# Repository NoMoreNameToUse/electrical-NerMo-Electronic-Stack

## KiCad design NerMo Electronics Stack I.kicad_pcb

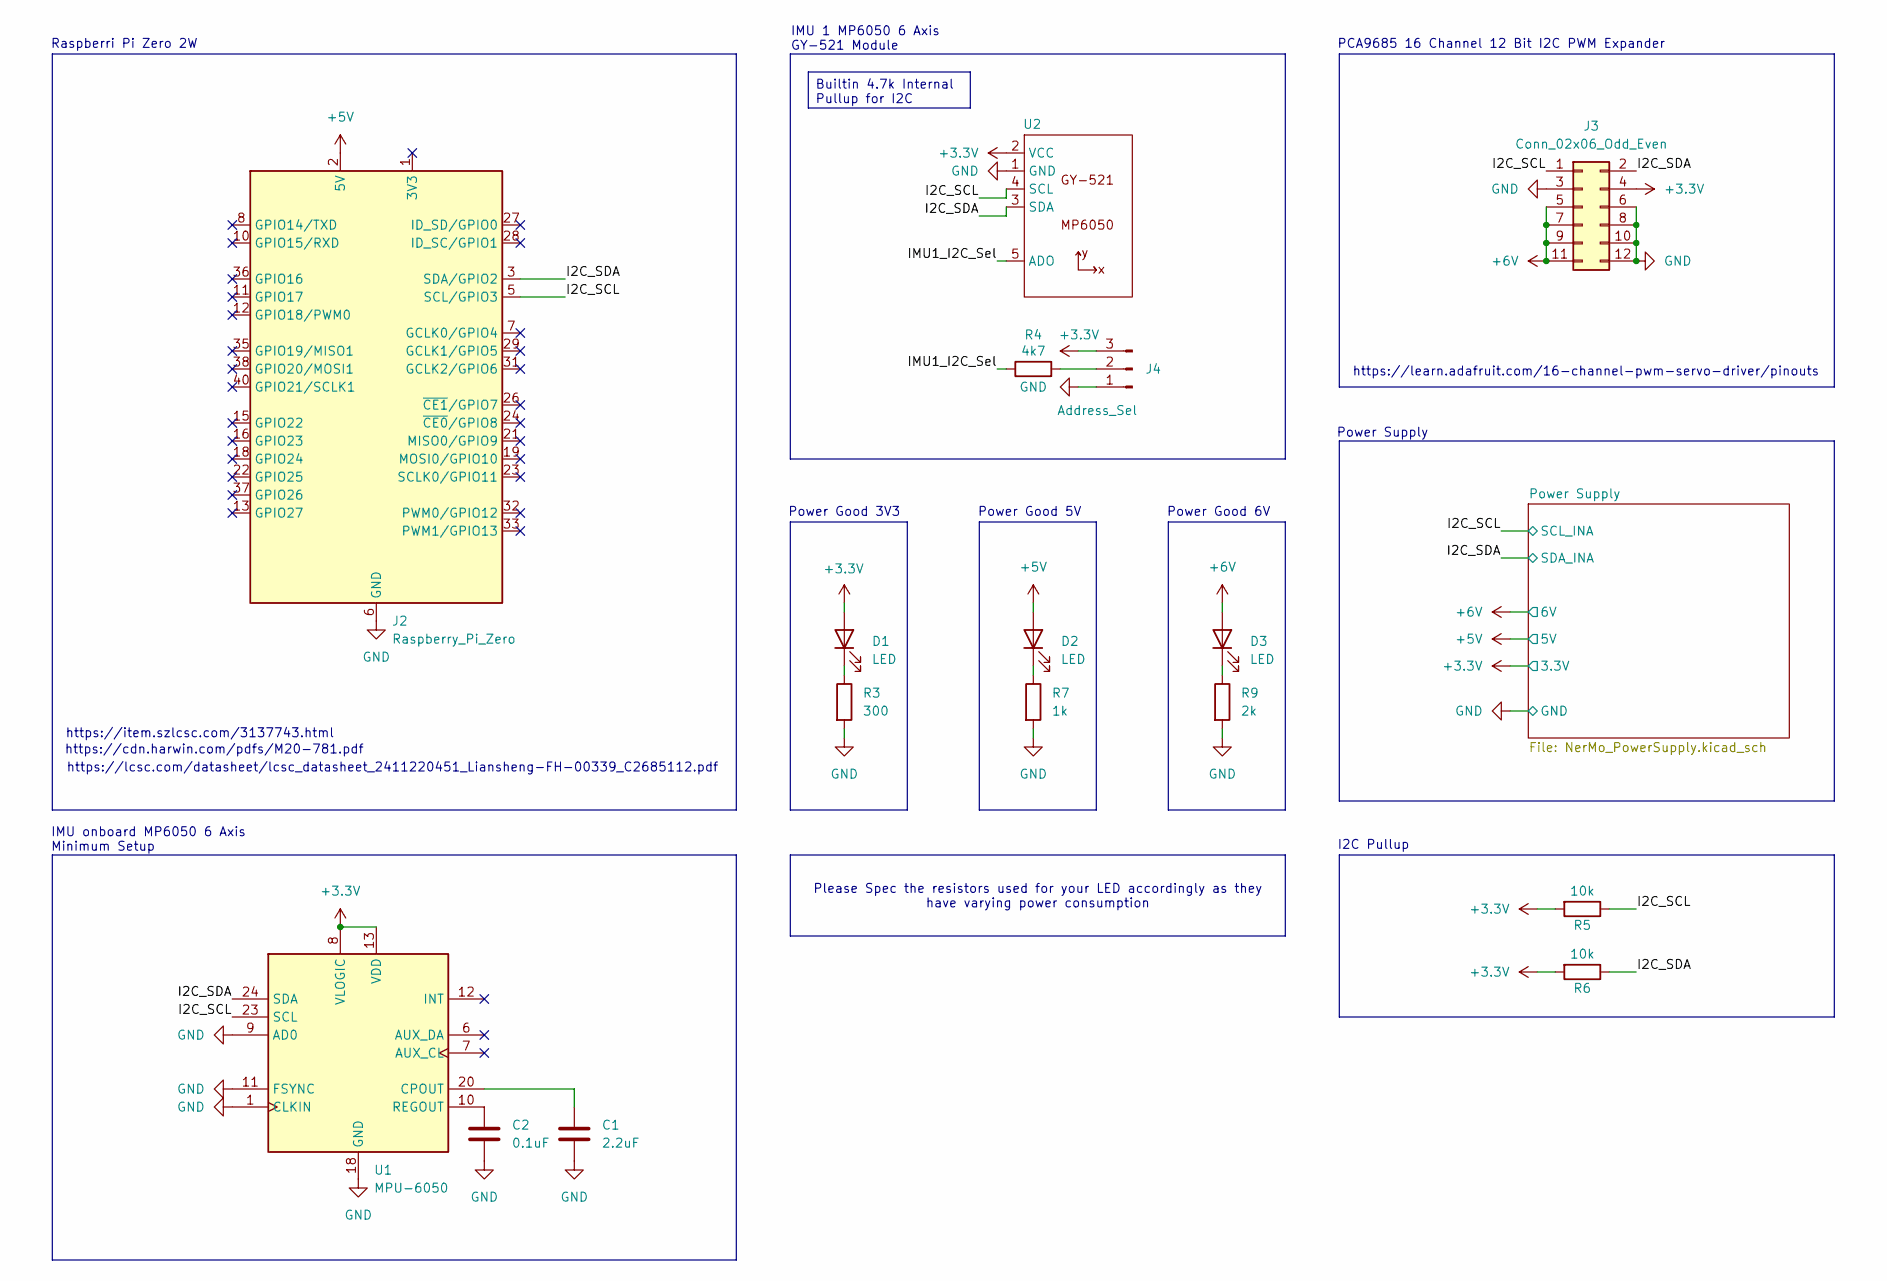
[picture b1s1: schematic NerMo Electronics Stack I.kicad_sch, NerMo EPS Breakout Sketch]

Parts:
C1: 2.2uF; C_0805_2012Metric
C2: 0.1uF; C_0805_2012Metric
D1, D2, D3: LED; LED_0805_2012Metric_Pad1.15x1.40mm_HandSolder
J2: Raspberry_Pi_Zero; Raspberry_Pi_Zero_2_W_HDR-TH
J3: Conn_02x06_Odd_Even; PinSocket_2x06_P1.27mm_Vertical
J4: Address_Sel; SolderJumper-3_P1.3mm_Open_Pad1.0x1.5mm
R3: 300; R_0805_2012Metric
R4: 4k7; R_0805_2012Metric
R5, R6: 10k; R_0805_2012Metric
R7: 1k; R_0805_2012Metric
R9: 2k; R_0805_2012Metric
U1: MPU-6050; InvenSense_QFN-24_4x4mm_P0.5mm
U2: PinHeader_1x05_P2.54mm_Vertical

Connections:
+3.3V: D1.2 (A), J3.4, J4.3, R5.2, R6.2, U1.8 (VLOGIC), U1.13 (VDD), U2.2 (VCC); also elsewhere on the board
+5V: D2.2 (A), J2.2 (5V), J2.4 (5V); also elsewhere on the board
+6V: D3.2 (A), J3.5, J3.7, J3.9, J3.11; also elsewhere on the board
/I2C_SCL: J2.5 (SCL/GPIO3), J3.1, R5.1, U1.23 (SCL), U2.4 (SCL); also elsewhere on the board
/I2C_SDA: J2.3 (SDA/GPIO2), J3.2, R6.1, U1.24 (SDA), U2.3 (SDA); also elsewhere on the board
/IMU1_I2C_Sel: R4.1, U2.5 (ADO)
GND: C1.2, C2.2, J2.6 (GND), J2.9 (GND), J2.14 (GND), J2.20 (GND), J2.25 (GND), J2.30 (GND), J2.34 (GND), J2.39 (GND), J3.3, J3.6, J3.8, J3.10, J3.12, J4.1, R3.2, R7.2, R9.2, U1.1 (CLKIN), U1.9 (AD0), U1.11 (FSYNC), U1.18 (GND), U2.1 (GND); also elsewhere on the board
unnamed: D1.1 (K), R3.1
unnamed: D2.1 (K), R7.1
unnamed: D3.1 (K), R9.1
unnamed: J4.2, R4.2
unnamed: C1.1, U1.20 (CPOUT)
unnamed: C2.1, U1.10 (REGOUT)

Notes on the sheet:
https://cdn.harwin.com/pdfs/M20-781.pdf
https://learn.adafruit.com/16-channel-pwm-servo-driver/pinouts
https://item.szlcsc.com/3137743.html
https://lcsc.com/datasheet/lcsc_datasheet_2411220451_Liansheng-FH-00339_C2685112.pdf
PCA9685 16 Channel 12 Bit I2C PWM Expander
Power Good 6V
IMU onboard MP6050 6 Axis Minimum Setup
Power Good 3V3
Raspberri Pi Zero 2W
I2C Pullup
IMU 1 MP6050 6 Axis GY-521 Module
Power Good 5V
Power Supply
Please Spec the resistors used for your LED accordingly as they have varying power consumption
Builtin 4.7k Internal Pullup for I2C

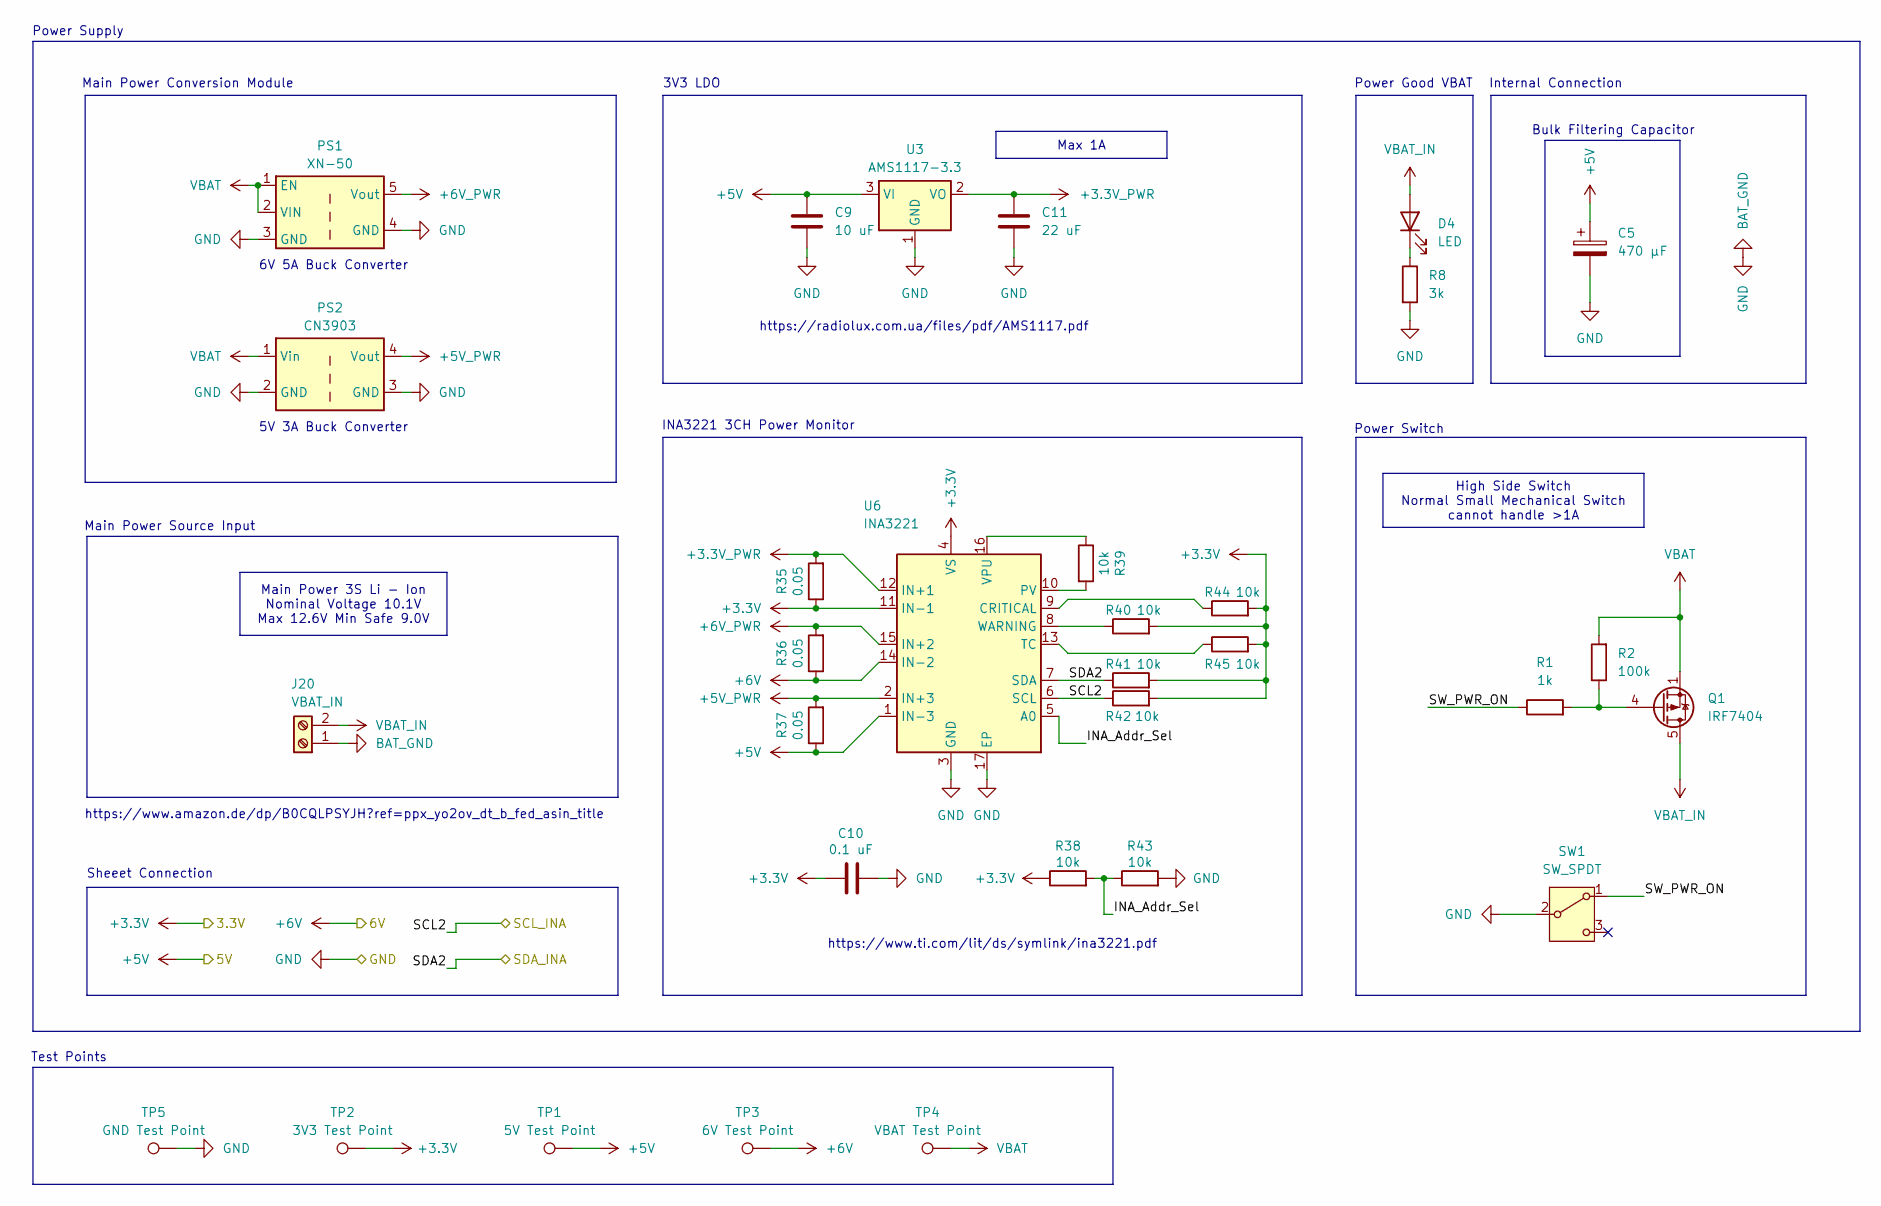
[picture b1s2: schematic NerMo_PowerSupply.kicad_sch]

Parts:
C5: 470 µF; CP_Elec_5x3
C9: 10 uF; C_0805_2012Metric
C10: 0.1 uF; C_0805_2012Metric
C11: 22 uF; C_0805_2012Metric
D4: LED; LED_0805_2012Metric_Pad1.15x1.40mm_HandSolder
J20: VBAT_IN; AMASS_XT30UPB-M_1x02_P5.0mm_Vertical
PS1: XN-50; XN-50 5A DCDC
PS2: CN3903; CN3903 3A DCDC
Q1: IRF7404; SOIC-8_3.9x4.9mm_P1.27mm
R1: 1k; R_0805_2012Metric
R2: 100k; R_0805_2012Metric
R8: 3k; R_0805_2012Metric
R35, R36, R37: 0.05; R_1206_3216Metric
R38, R39, R40, R41, R42, R43, R44, R45: 10k; R_0805_2012Metric
SW1: SW_SPDT; SW_SPDT_PCM12
TP1: 5V Test Point; TestPoint_Pad_2.0x2.0mm
TP2: 3V3 Test Point; TestPoint_Pad_2.0x2.0mm
TP3: 6V Test Point; TestPoint_Pad_2.0x2.0mm
TP4: VBAT Test Point; TestPoint_Pad_2.0x2.0mm
TP5: GND Test Point; TestPoint_Pad_2.0x2.0mm
U3: AMS1117-3.3; SOT-223-3_TabPin2
U6: INA3221; Texas_RGV0016A_VQFN-16-1EP_4x4mm_P0.65mm_EP2.1x2.1mm

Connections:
+3.3V: C10.1, R35.1, R38.1, R40.2, R41.2, R42.2, R44.2, R45.2, TP2.1, U6.4 (VS), U6.11 (IN-1); also elsewhere on the board
+3.3V_PWR: C11.1, R35.2, U3.2 (VO), U6.12 (IN+1)
+5V: C5.1, C9.1, R37.1, TP1.1, U3.3 (VI), U6.1 (IN-3); also elsewhere on the board
+5V_PWR: PS2.4 (Vout), R37.2, U6.2 (IN+3)
+6V: R36.1, TP3.1, U6.14 (IN-2); also elsewhere on the board
+6V_PWR: PS1.5 (Vout), R36.2, U6.15 (IN+2)
/I2C_SCL: R42.1, U6.6 (SCL); also elsewhere on the board
/I2C_SDA: R41.1, U6.7 (SDA); also elsewhere on the board
/Power Supply/INA_Addr_Sel: R38.2, R43.1, U6.5 (A0)
/Power Supply/SW_PWR_ON: R1.1, SW1.1 (A)
GND: C5.2, C9.2, C10.2, C11.2, J20.1, PS1.3 (GND), PS1.4 (GND), PS2.2 (GND), PS2.3 (GND), R8.2, R43.2, SW1.2 (B), TP5.1, U3.1 (GND), U6.3 (GND), U6.17 (EP); also elsewhere on the board
unnamed: D4.1 (K), R8.1
unnamed: Q1.4 (G), R1.2, R2.1
unnamed: R44.1, U6.9 (CRITICAL)
unnamed: R39.2, U6.10 (PV)
unnamed: R45.1, U6.13 (TC)
unnamed: R39.1, U6.16 (VPU)
unnamed: R40.1, U6.8 (WARNING)
VBAT: PS1.1 (EN), PS1.2 (VIN), PS2.1 (Vin), Q1.1 (S), Q1.2 (S), Q1.3 (S), R2.2, TP4.1
VBAT_IN: D4.2 (A), J20.2, Q1.5 (D), Q1.6 (D), Q1.7 (D), Q1.8 (D)

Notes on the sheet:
3V3 LDO
Main Power Source Input
INA3221 3CH Power Monitor
https://www.ti.com/lit/ds/symlink/ina3221.pdf
Test Points
5V 3A Buck Converter
Bulk Filtering Capacitor
Internal Connection
6V 5A Buck Converter
Power Switch
https://radiolux.com.ua/files/pdf/AMS1117.pdf
Power Good VBAT
Power Supply
Sheeet Connection
https://www.amazon.de/dp/B0CQLPSYJH?ref=ppx_yo2ov_dt_b_fed_asin_title
Main Power Conversion Module
Main Power 3S Li - Ion Nominal Voltage 10.1V Max 12.6V Min Safe 9.0V
Max 1A
High Side Switch Normal Small Mechanical Switch cannot handle >1A

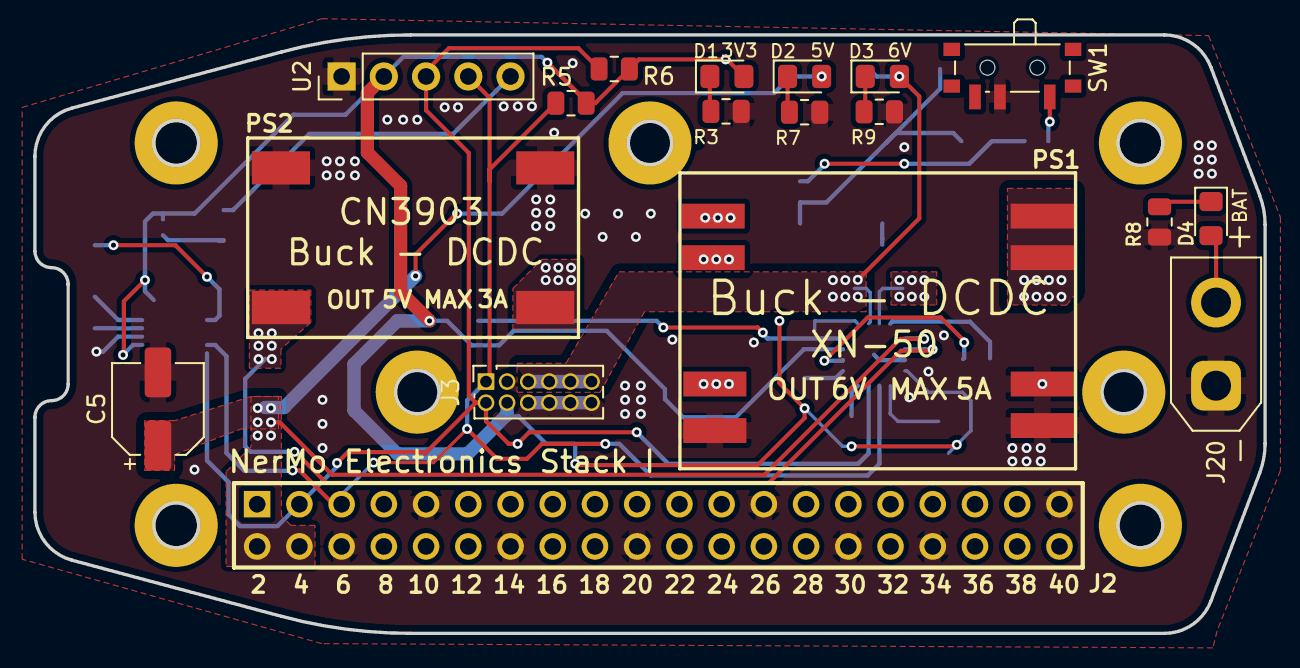
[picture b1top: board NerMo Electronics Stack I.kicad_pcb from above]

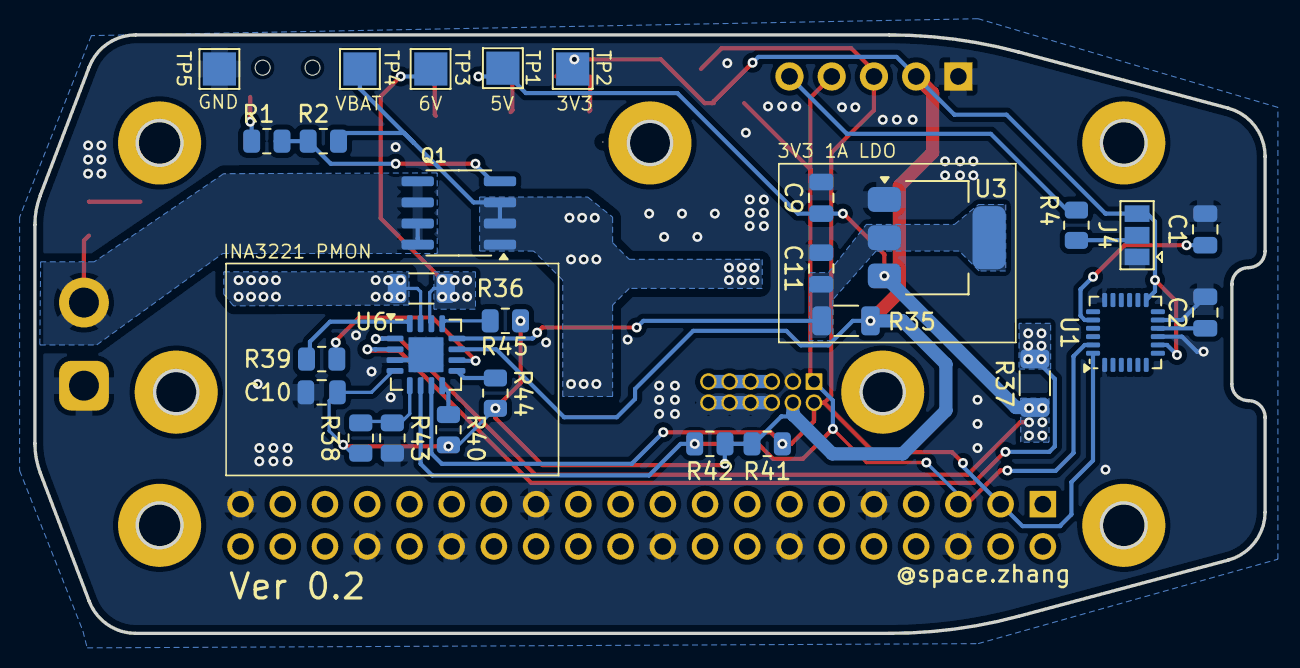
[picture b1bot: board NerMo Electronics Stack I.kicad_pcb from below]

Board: 2 copper layers, 74.0 x 36.0 mm, 54 parts (29 on the bottom side), 27 nets.

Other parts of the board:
*REF: (no value)
*REF#2, *REF#3, *REF#4, *REF#5, *REF#6, *REF#7: (no value)

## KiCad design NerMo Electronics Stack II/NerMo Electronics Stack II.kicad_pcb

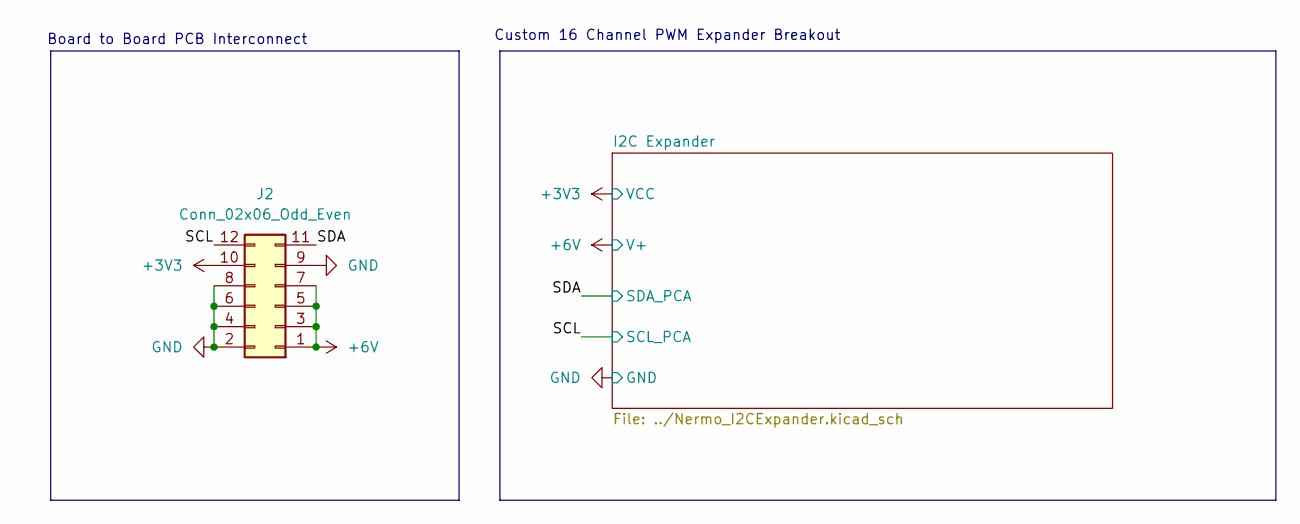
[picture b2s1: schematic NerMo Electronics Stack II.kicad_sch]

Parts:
J2: Conn_02x06_Odd_Even; PinHeader_2x06_P1.27mm_Vertical

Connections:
+3V3: J2.10; also elsewhere on the board
+6V: J2.1, J2.3, J2.5, J2.7; also elsewhere on the board
/SCL: J2.12; also elsewhere on the board
/SDA: J2.11; also elsewhere on the board
GND: J2.2, J2.4, J2.6, J2.8, J2.9; also elsewhere on the board

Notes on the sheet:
Board to Board PCB Interconnect
Custom 16 Channel PWM Expander Breakout

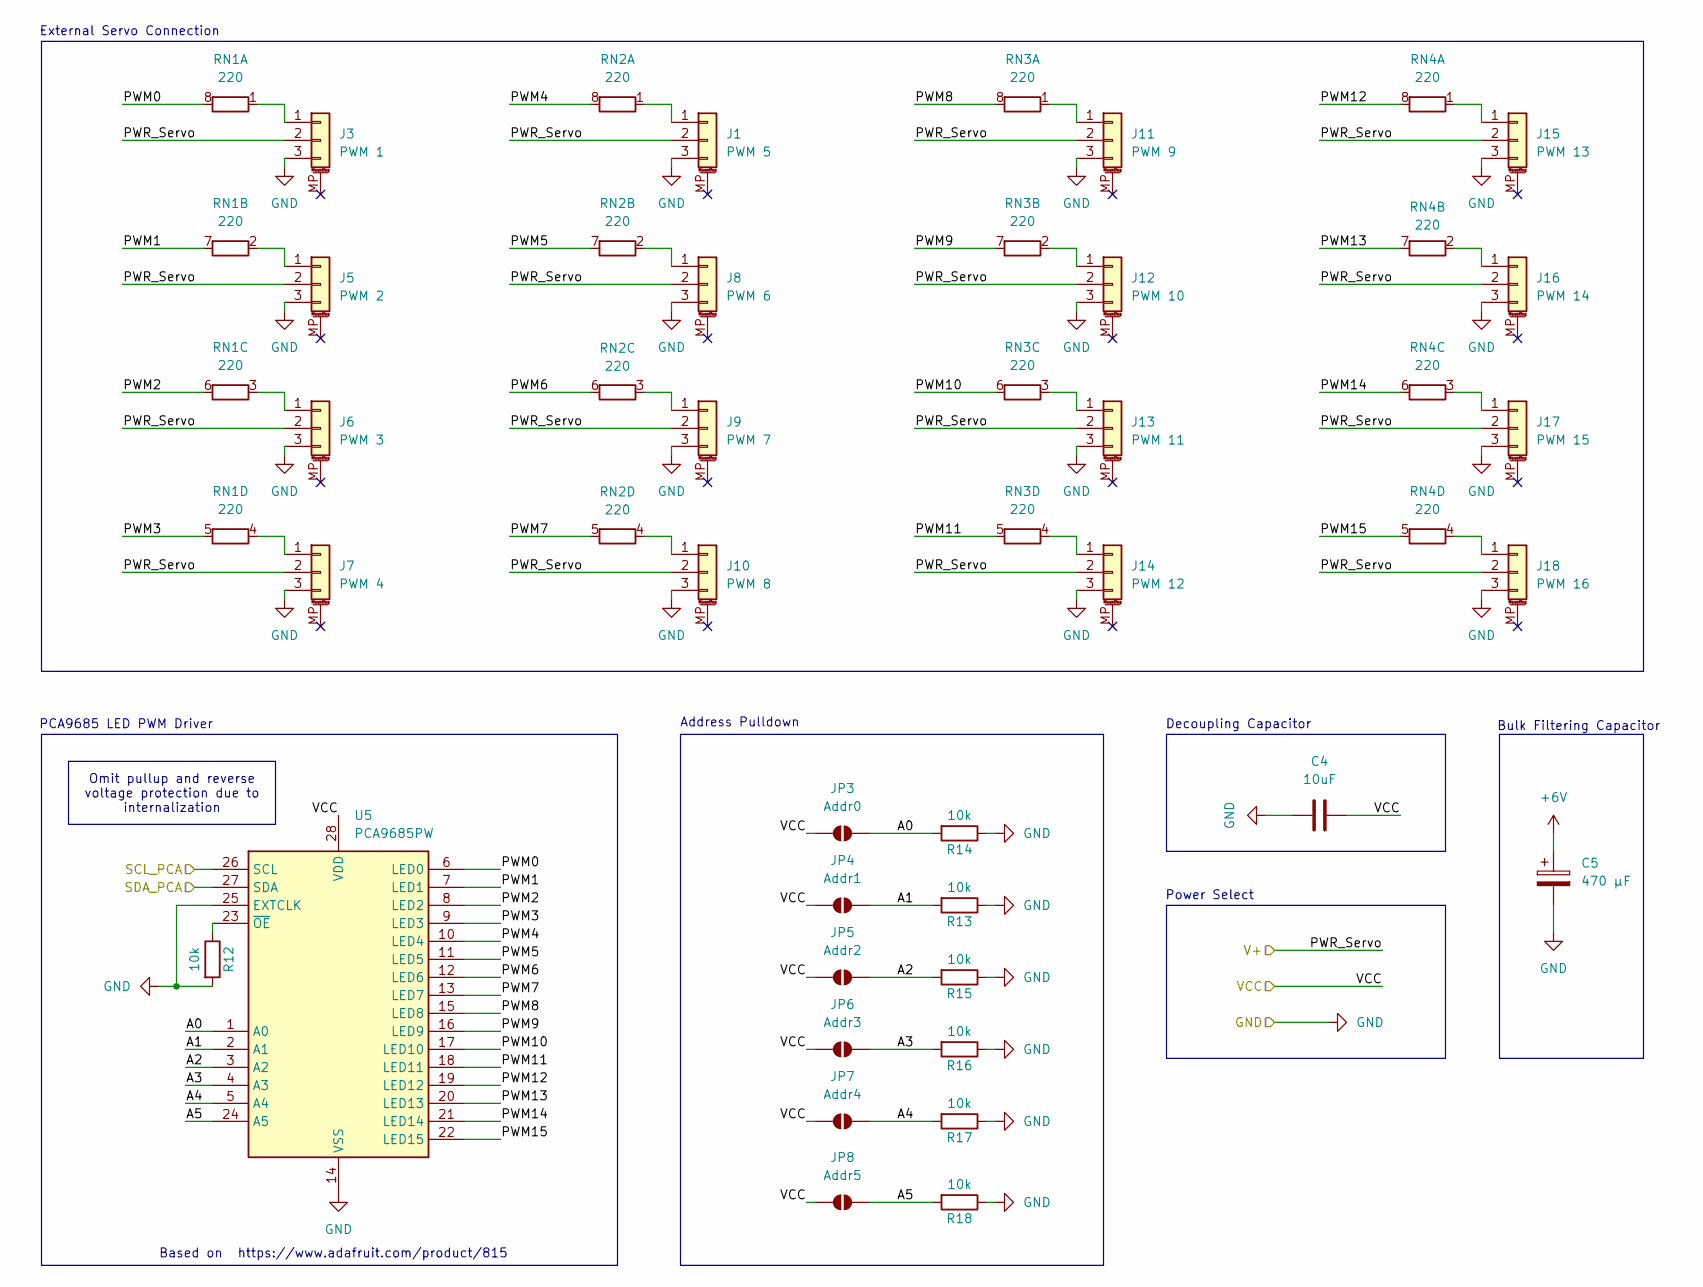
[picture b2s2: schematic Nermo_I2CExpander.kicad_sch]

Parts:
C4: 10uF; C_0603_1608Metric
C5: 470 µF; CP_EIA-7360-38_Kemet-E_HandSolder
J1: PWM 5; JST_SH_SM03B-SRSS-TB_1x03-1MP_P1.00mm_Horizontal
J3: PWM 1; JST_SH_SM03B-SRSS-TB_1x03-1MP_P1.00mm_Horizontal
J5: PWM 2; JST_SH_SM03B-SRSS-TB_1x03-1MP_P1.00mm_Horizontal
J6: PWM 3; JST_SH_SM03B-SRSS-TB_1x03-1MP_P1.00mm_Horizontal
J7: PWM 4; JST_SH_SM03B-SRSS-TB_1x03-1MP_P1.00mm_Horizontal
J8: PWM 6; JST_SH_SM03B-SRSS-TB_1x03-1MP_P1.00mm_Horizontal
J9: PWM 7; JST_SH_SM03B-SRSS-TB_1x03-1MP_P1.00mm_Horizontal
J10: PWM 8; JST_SH_SM03B-SRSS-TB_1x03-1MP_P1.00mm_Horizontal
J11: PWM 9; JST_SH_SM03B-SRSS-TB_1x03-1MP_P1.00mm_Horizontal
J12: PWM 10; JST_SH_SM03B-SRSS-TB_1x03-1MP_P1.00mm_Horizontal
J13: PWM 11; JST_SH_SM03B-SRSS-TB_1x03-1MP_P1.00mm_Horizontal
J14: PWM 12; JST_SH_SM03B-SRSS-TB_1x03-1MP_P1.00mm_Horizontal
J15: PWM 13; JST_SH_BM03B-SRSS-TB_1x03-1MP_P1.00mm_Vertical
J16: PWM 14; JST_SH_BM03B-SRSS-TB_1x03-1MP_P1.00mm_Vertical
J17: PWM 15; JST_SH_BM03B-SRSS-TB_1x03-1MP_P1.00mm_Vertical
J18: PWM 16; JST_SH_BM03B-SRSS-TB_1x03-1MP_P1.00mm_Vertical
JP3: Addr0; SolderJumper-2_P1.3mm_Open_TrianglePad1.0x1.5mm
JP4: Addr1; SolderJumper-2_P1.3mm_Open_TrianglePad1.0x1.5mm
JP5: Addr2; SolderJumper-2_P1.3mm_Open_TrianglePad1.0x1.5mm
JP6: Addr3; SolderJumper-2_P1.3mm_Open_TrianglePad1.0x1.5mm
JP7: Addr4; SolderJumper-2_P1.3mm_Open_TrianglePad1.0x1.5mm
JP8: Addr5; SolderJumper-2_P1.3mm_Open_TrianglePad1.0x1.5mm
R12, R13, R14, R15, R16, R17, R18: 10k; R_0603_1608Metric
RN1, RN2, RN3, RN4: 220; R_Array_Concave_4x0603
U5: PCA9685PW; TSSOP-28_4.4x9.7mm_P0.65mm

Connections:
+3V3: C4.2, JP3.2 (B), JP4.2 (B), JP5.2 (B), JP6.2 (B), JP7.2 (B), JP8.2 (B), U5.28 (VDD); also elsewhere on the board
+6V: J1.2, J3.2, J5.2, J6.2, J7.2, J8.2, J9.2, J10.2, J11.2, J12.2, J13.2, J14.2, J15.2, J16.2, J17.2, J18.2; also elsewhere on the board
/I2C Expander/A0: JP3.1 (A), R14.2, U5.1 (A0)
/I2C Expander/A1: JP4.1 (A), R13.2, U5.2 (A1)
/I2C Expander/A2: JP5.1 (A), R15.2, U5.3 (A2)
/I2C Expander/A3: JP6.1 (A), R16.2, U5.4 (A3)
/I2C Expander/A4: JP7.1 (A), R17.2, U5.5 (A4)
/I2C Expander/A5: JP8.1 (A), R18.2, U5.24 (A5)
/I2C Expander/PWM0: RN1.8 (R1.2), U5.6 (LED0)
/I2C Expander/PWM1: RN1.7 (R2.2), U5.7 (LED1)
/I2C Expander/PWM2: RN1.6 (R3.2), U5.8 (LED2)
/I2C Expander/PWM3: RN1.5 (R4.2), U5.9 (LED3)
/I2C Expander/PWM4: RN2.8 (R1.2), U5.10 (LED4)
/I2C Expander/PWM5: RN2.7 (R2.2), U5.11 (LED5)
/I2C Expander/PWM6: RN2.6 (R3.2), U5.12 (LED6)
/I2C Expander/PWM7: RN2.5 (R4.2), U5.13 (LED7)
/I2C Expander/PWM8: RN3.8 (R1.2), U5.15 (LED8)
/I2C Expander/PWM9: RN3.7 (R2.2), U5.16 (LED9)
/I2C Expander/PWM10: RN3.6 (R3.2), U5.17 (LED10)
/I2C Expander/PWM11: RN3.5 (R4.2), U5.18 (LED11)
/I2C Expander/PWM12: RN4.8 (R1.2), U5.19 (LED12)
/I2C Expander/PWM13: RN4.7 (R2.2), U5.20 (LED13)
/I2C Expander/PWM14: RN4.6 (R3.2), U5.21 (LED14)
/I2C Expander/PWM15: RN4.5 (R4.2), U5.22 (LED15)
/SCL: U5.26 (SCL); also elsewhere on the board
/SDA: U5.27 (SDA); also elsewhere on the board
GND: C4.1, C5.2, J1.3, J3.3, J5.3, J6.3, J7.3, J8.3, J9.3, J10.3, J11.3, J12.3, J13.3, J14.3, J15.3, J16.3, J17.3, J18.3, R12.2, R13.1, R14.1, R15.1, R16.1, R17.1, R18.1, U5.14 (VSS), U5.25 (EXTCLK); also elsewhere on the board
unnamed: J1.1, RN2.1 (R1.1)
unnamed: J3.1, RN1.1 (R1.1)
unnamed: J5.1, RN1.2 (R2.1)
unnamed: J6.1, RN1.3 (R3.1)
unnamed: J7.1, RN1.4 (R4.1)
unnamed: J8.1, RN2.2 (R2.1)
unnamed: J9.1, RN2.3 (R3.1)
unnamed: J10.1, RN2.4 (R4.1)
unnamed: J11.1, RN3.1 (R1.1)
unnamed: J12.1, RN3.2 (R2.1)
unnamed: J13.1, RN3.3 (R3.1)
unnamed: J14.1, RN3.4 (R4.1)
unnamed: J15.1, RN4.1 (R1.1)
unnamed: J16.1, RN4.2 (R2.1)
unnamed: J17.1, RN4.3 (R3.1)
unnamed: J18.1, RN4.4 (R4.1)
unnamed: R12.1, U5.23 (~OE)

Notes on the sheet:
PCA9685 LED PWM Driver
Decoupling Capacitor
https://www.adafruit.com/product/815
Based on
External Servo Connection
Power Select
Bulk Filtering Capacitor
Address Pulldown
Omit pullup and reverse voltage protection due to internalization

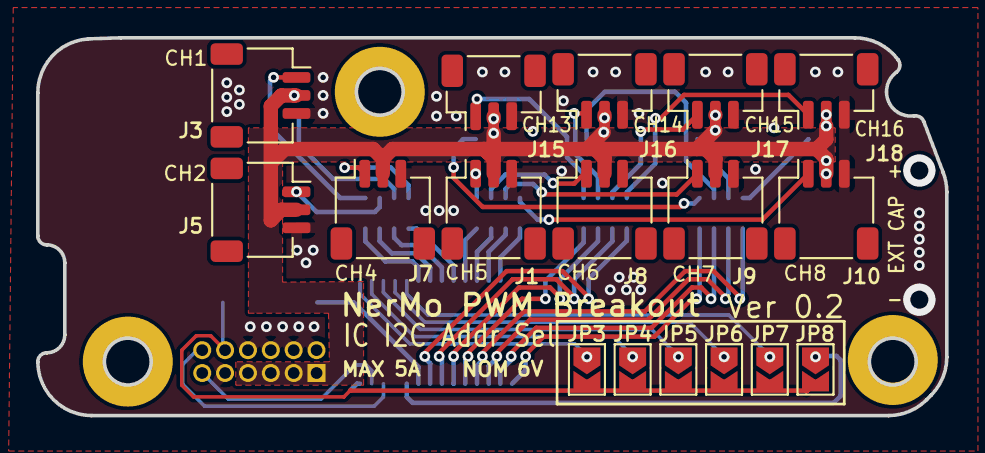
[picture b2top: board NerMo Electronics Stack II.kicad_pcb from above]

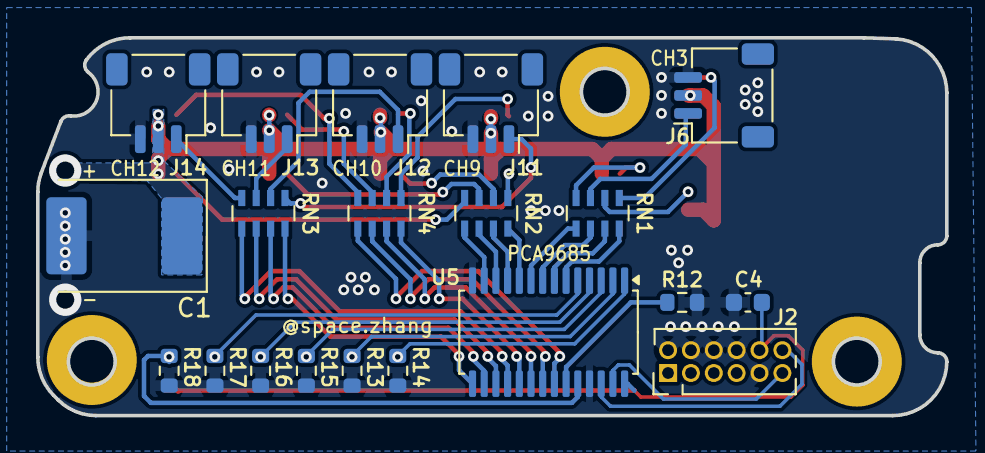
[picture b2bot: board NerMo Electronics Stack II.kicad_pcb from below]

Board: 2 copper layers, 50.5 x 21.0 mm, 37 parts (20 on the bottom side), 44 nets.

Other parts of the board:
C1: 470 µF; CP_EIA-7360-38_Kemet-E_HandSolder

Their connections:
+6V: C1.1; also elsewhere on the board
GND: C1.2; also elsewhere on the board

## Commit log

2025-09-13 feat: initial upload
2025-09-15 feat: NerMo Stack V1
2025-09-15 fix: fixed breakout interconnect pinout
2025-09-17 fix: fixed external IMU Connector positioning
2025-09-19 feat: V0.2
